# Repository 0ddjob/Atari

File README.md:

# Atari
Projects for the Atari 400/800 & 2600.<br>

## Custom Star Raiders Video Touch Pad
Star Raiders only uses five of the 12 possible buttons so I thought it *might* be interesting to make a custom controller.  It's pretty simple.<br>

{Fri 15-Sept-2023}<br>
Sent board prototype for fabrication<br>

## Video Touch Pad
Re-creation of the full 12-button Video Touch Pad.<br>

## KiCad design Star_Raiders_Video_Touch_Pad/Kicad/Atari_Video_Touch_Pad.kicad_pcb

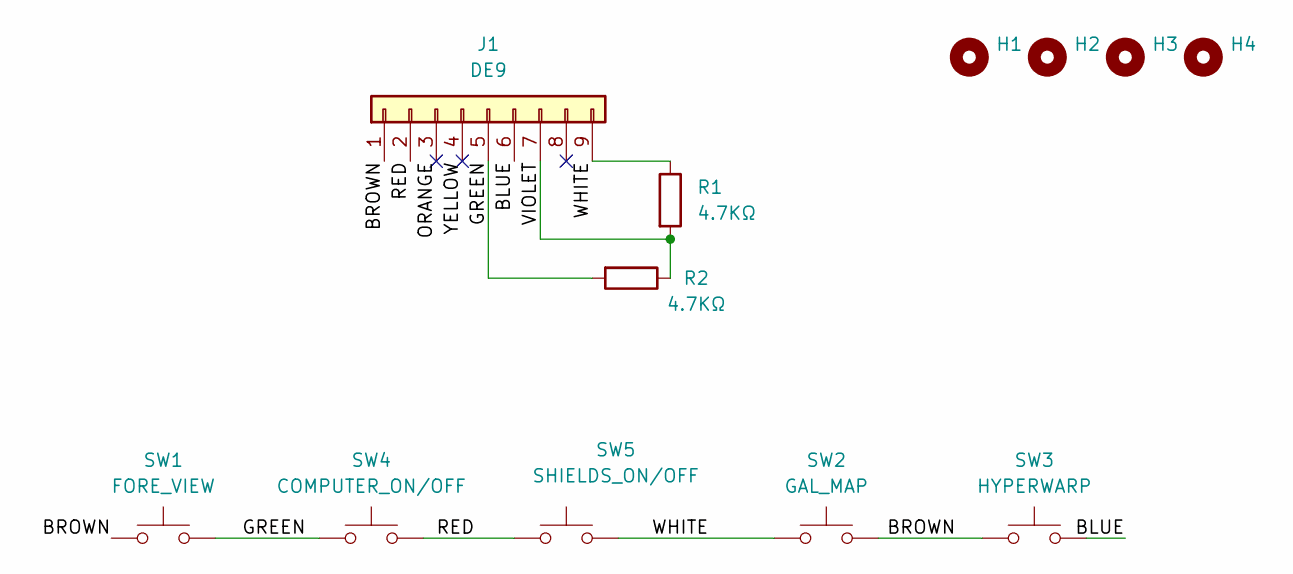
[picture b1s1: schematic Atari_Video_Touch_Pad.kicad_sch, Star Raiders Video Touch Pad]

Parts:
H1, H2, H3, H4: MountingHole; MountingHole_3.2mm_M3
J1: DE9; PinHeader_1x09_P2.54mm_Horizontal
R1, R2: 4.7KΩ; R_Axial_DIN0207_L6.3mm_D2.5mm_P7.62mm_Horizontal
SW1: FORE_VIEW; SW_Cherry_MX_PCB_1.00u
SW2: GAL_MAP; SW_Cherry_MX_PCB_1.00u
SW3: HYPERWARP; SW_Cherry_MX_PCB_1.00u
SW4: COMPUTER_ON/OFF; SW_Cherry_MX_PCB_1.00u
SW5: SHIELDS_ON/OFF; SW_Cherry_MX_PCB_1.00u

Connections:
/BLUE: J1.6, SW3.2
/BROWN: J1.1, SW1.1, SW2.2, SW3.1
/GREEN: J1.5, R2.2, SW1.2, SW4.1
/ORANGE: J1.3
/RED: J1.2, SW4.2, SW5.1
/VIOLET: J1.7, R1.2, R2.1
/WHITE: J1.9, R1.1, SW2.1, SW5.2
/YELLOW: J1.4

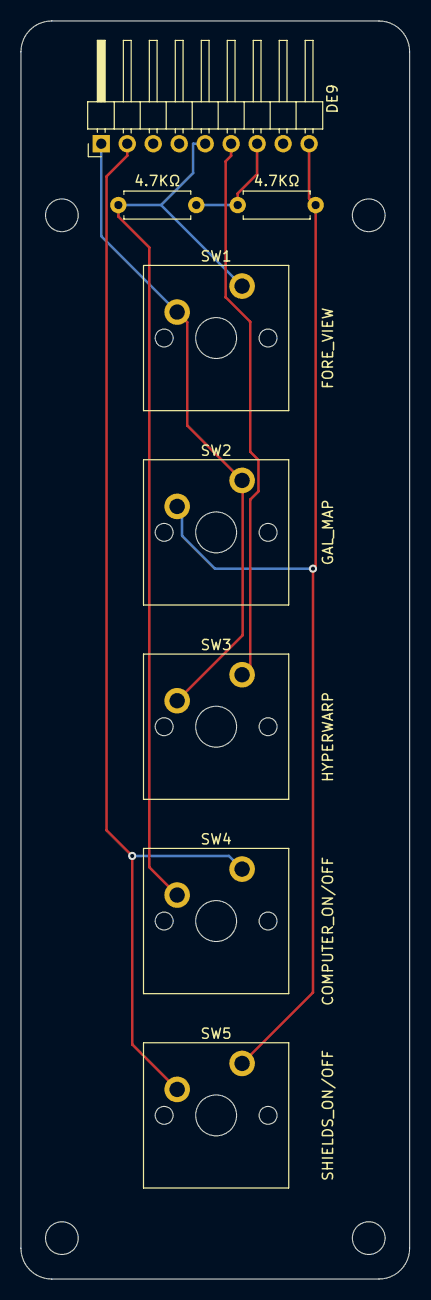
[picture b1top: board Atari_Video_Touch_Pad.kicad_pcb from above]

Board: 2 copper layers, 38.0 x 123.0 mm, 12 parts (0 on the bottom side), 6 nets.

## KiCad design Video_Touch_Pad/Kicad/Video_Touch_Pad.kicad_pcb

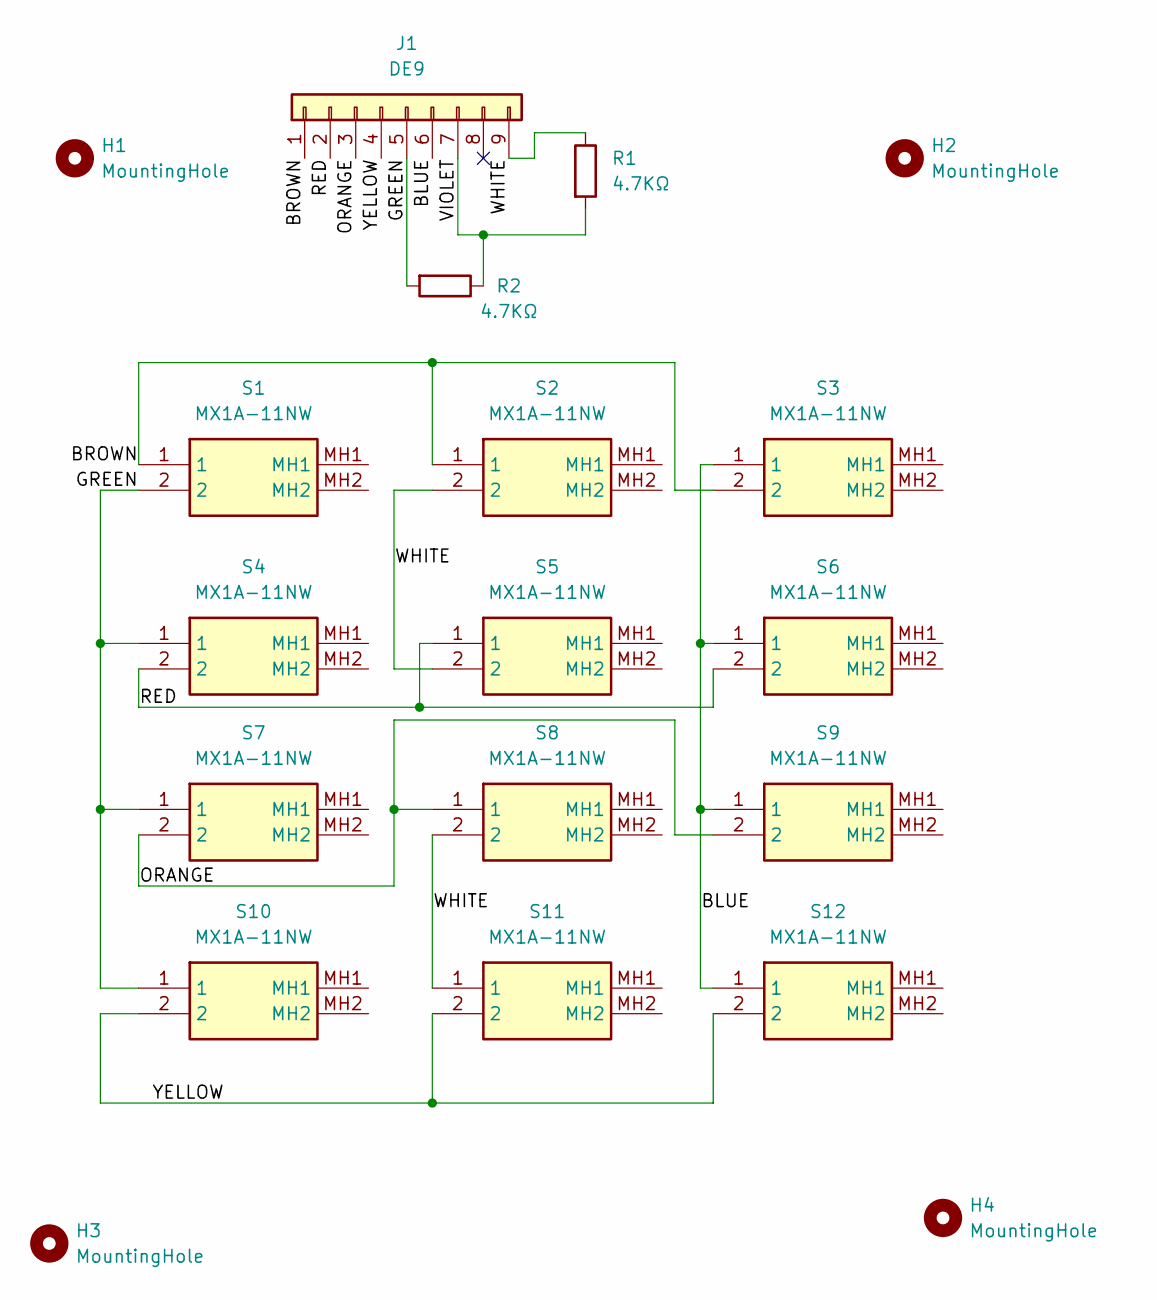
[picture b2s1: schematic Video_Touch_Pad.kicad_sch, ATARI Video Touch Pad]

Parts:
H1, H2, H3, H4: MountingHole; MountingHole_3.2mm_M3
J1: DE9; PinHeader_1x09_P2.54mm_Horizontal
R1, R2: 4.7KΩ; R_Axial_DIN0207_L6.3mm_D2.5mm_P7.62mm_Horizontal
S1, S2, S3, S4, S5, S6, S7, S8, S9, S10, S11, S12: MX1A-11NW; MX1A11NW; Mouser Part Number 540-MX1A-11NW

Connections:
/BLUE: J1.6, S3.1, S6.1, S9.1, S12.1
/BROWN: J1.1, S1.1, S2.1, S3.2
/GREEN: J1.5, R2.2, S1.2, S4.1, S7.1, S10.1
/ORANGE: J1.3, S7.2, S8.1, S9.2
/RED: J1.2, S4.2, S5.1, S6.2
/VIOLET: J1.7, R1.2, R2.1
/WHITE: J1.9, R1.1, S2.2, S5.2, S8.2, S11.1
/YELLOW: J1.4, S10.2, S11.2, S12.2

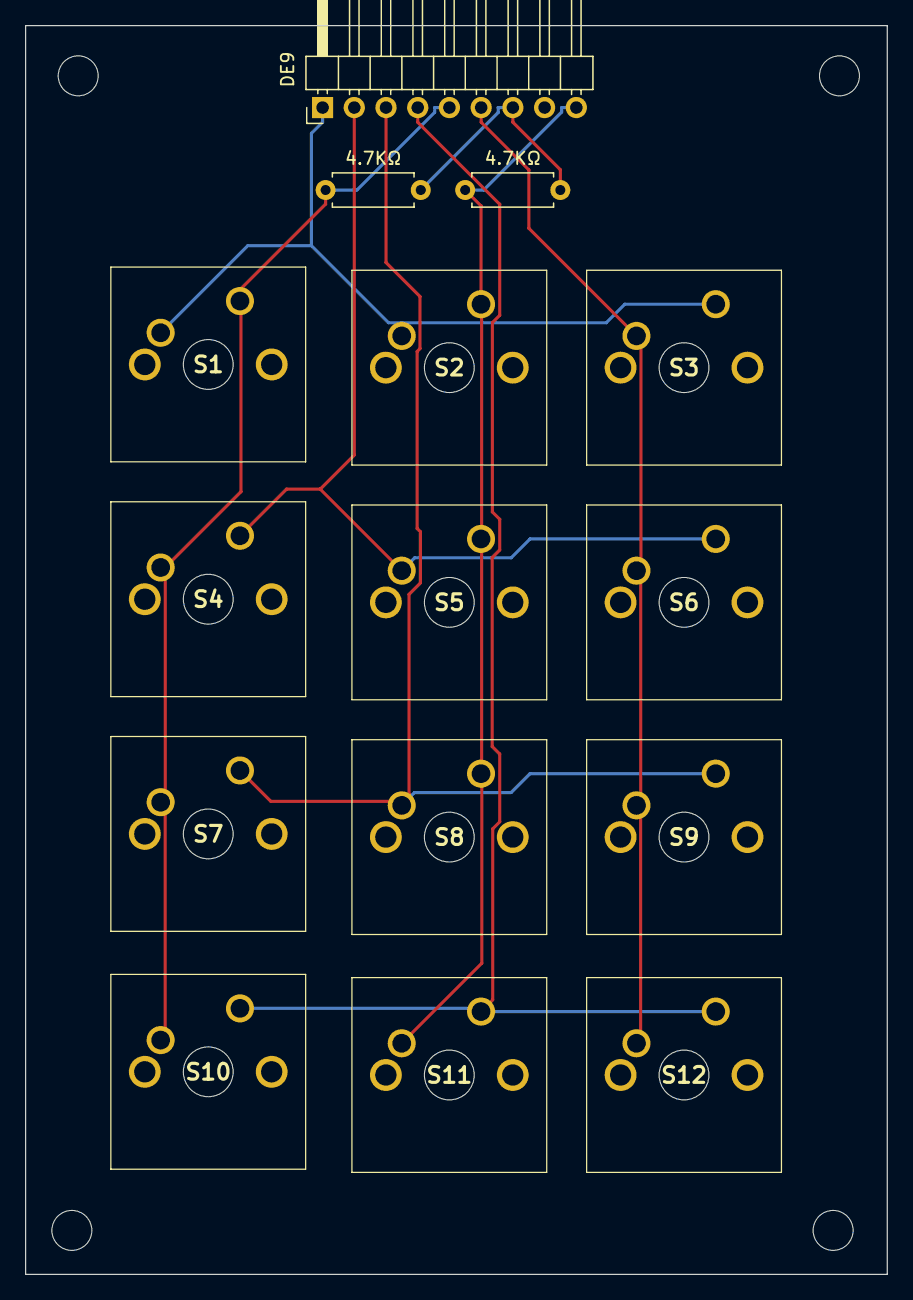
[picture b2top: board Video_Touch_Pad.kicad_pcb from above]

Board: 2 copper layers, 69.0 x 100.0 mm, 19 parts (0 on the bottom side), 8 nets.

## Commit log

2023-09-11 Initial
2023-09-11 Added images
2023-09-11 Added full 12-key Video Touch Pad
2023-09-11 Resized image
2023-09-13 Added mounting holes
2023-09-13 Moved schematic PDF
2023-09-15 Sent board prototype for fabrication
2025-03-26 Improved design (maybe?)
